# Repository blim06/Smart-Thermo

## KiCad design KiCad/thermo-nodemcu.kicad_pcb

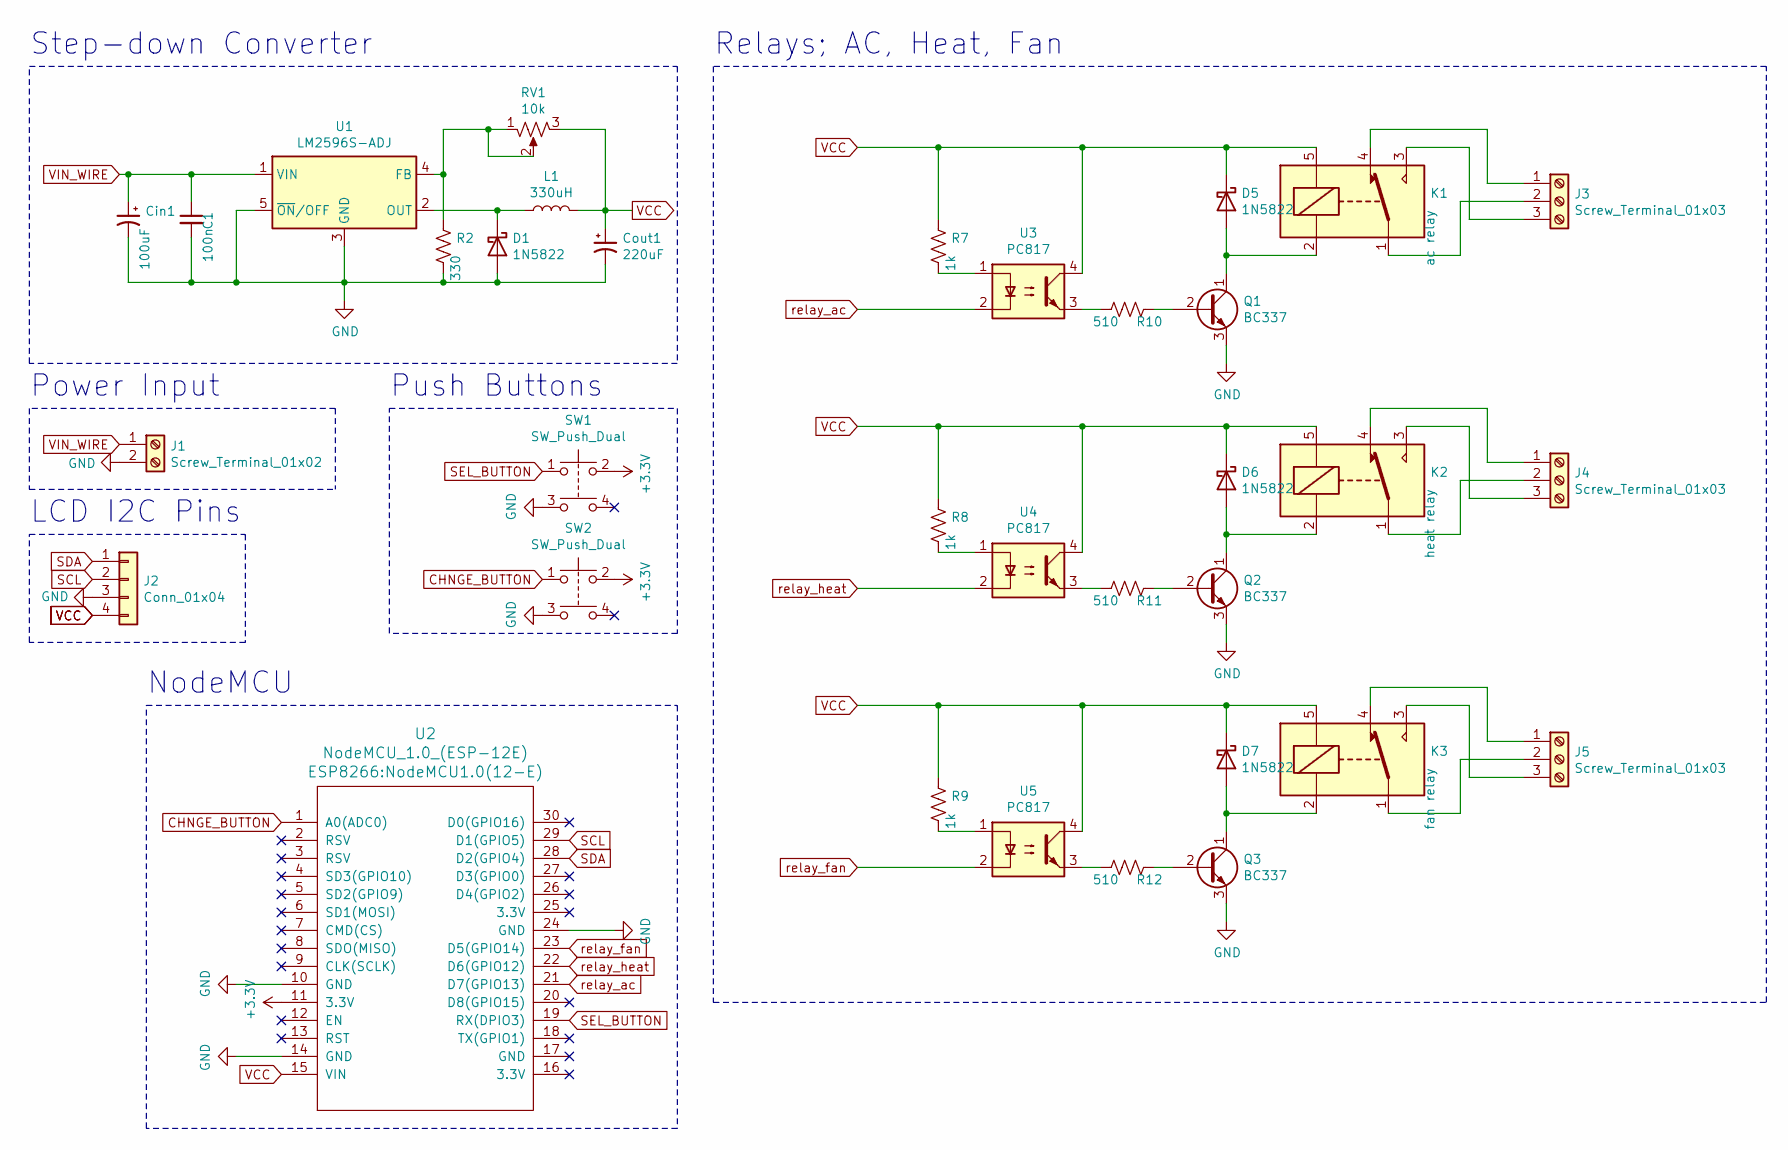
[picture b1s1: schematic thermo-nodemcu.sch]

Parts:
C1: 100n; C_0805_2012Metric
Cin1: 100uF; CP_Radial_D8.0mm_P3.50mm
Cout1: 220uF; CP_Radial_D6.3mm_P2.50mm
D1, D5, D6, D7: 1N5822; D_DO-201AD_P15.24mm_Horizontal
J1: Screw_Terminal_01x02; Altech_AK300_1x02_P5.00mm_45-Degree
J2: Conn_01x04; PinSocket_1x04_P1.27mm_Vertical
J3, J4, J5: Screw_Terminal_01x03; Altech_AK300_1x03_P5.00mm_45-Degree
K1: ac relay; Relay_SPDT_SANYOU_SRD_Series_Form_C
K2: heat relay; Relay_SPDT_SANYOU_SRD_Series_Form_C
K3: fan relay; Relay_SPDT_SANYOU_SRD_Series_Form_C
L1: 330uH; L_0805_2012Metric
Q1, Q2, Q3: BC337; TO-92_Inline
R2: 330; R_0805_2012Metric
R7, R8, R9: 1k; R_0805_2012Metric
R10, R11, R12: 510; R_0805_2012Metric
RV1: 10k; Potentiometer_Bourns_3296W_Vertical
SW1, SW2: SW_Push_Dual; PinSocket_2x02_P1.27mm_Vertical
U1: LM2596S-ADJ; TO-263-5_TabPin3
U2: NodeMCU_1.0_(ESP-12E); NodeMCU1.0(12-E)
U3, U4, U5: PC817; DIP-4_W7.62mm

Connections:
+3V3: SW1.2, SW2.2, U2.11 (3.3V)
CHNGE_BUTTON: SW2.1, U2.1 (A0(ADC0))
GND: C1.2, Cin1.2, Cout1.2, D1.2 (A), J1.2, J2.3, Q1.3 (E), Q2.3 (E), Q3.3 (E), R2.2, SW1.3, SW2.3, U1.3 (GND), U1.5 (~ON~/OFF), U2.10 (GND), U2.14 (GND), U2.24 (GND)
unnamed: D1.1 (K), L1.2, U1.2 (OUT)
unnamed: D5.2 (A), K1.2, Q1.1 (C)
unnamed: D6.2 (A), K2.2, Q2.1 (C)
unnamed: D7.2 (A), K3.2, Q3.1 (C)
unnamed: J3.1, K1.4
unnamed: J3.2, K1.1
unnamed: J3.3, K1.3
unnamed: J4.1, K2.4
unnamed: J4.2, K2.1
unnamed: J4.3, K2.3
unnamed: J5.1, K3.4
unnamed: J5.2, K3.1
unnamed: J5.3, K3.3
unnamed: Q1.2 (B), R10.1
unnamed: Q2.2 (B), R11.1
unnamed: Q3.2 (B), R12.1
unnamed: R2.1, RV1.1, RV1.2, U1.4 (FB)
unnamed: R7.2, U3.1
unnamed: R8.2, U4.1
unnamed: R9.2, U5.1
unnamed: R10.2, U3.3
unnamed: R11.2, U4.3
unnamed: R12.2, U5.3
SCL: J2.2, U2.29 (D1(GPIO5))
SDA: J2.1, U2.28 (D2(GPIO4))
SEL_BUTTON: SW1.1, U2.19 (RX(DPIO3))
VCC: Cout1.1, D5.1 (K), D6.1 (K), D7.1 (K), J2.4, K1.5, K2.5, K3.5, L1.1, R7.1, R8.1, R9.1, RV1.3, U2.15 (VIN), U3.4, U4.4, U5.4
VIN_WIRE: C1.1, Cin1.1, J1.1, U1.1 (VIN)
relay_ac: U2.21 (D7(GPIO13)), U3.2
relay_fan: U2.23 (D5(GPIO14)), U5.2
relay_heat: U2.22 (D6(GPIO12)), U4.2

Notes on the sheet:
Power Input
Push Buttons
Relays; AC, Heat, Fan
Step-down Converter
LCD I2C Pins
NodeMCU

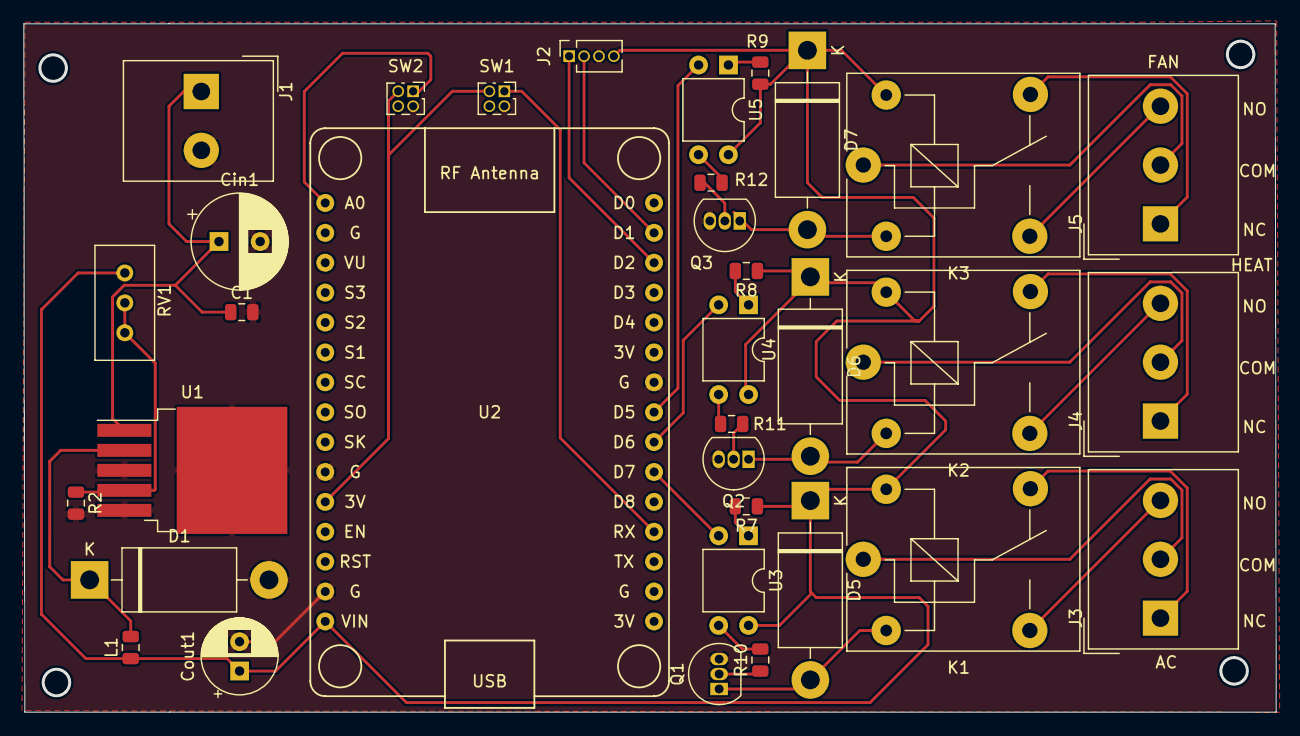
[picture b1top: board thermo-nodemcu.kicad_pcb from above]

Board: 2 copper layers, 106.4 x 58.5 mm, 34 parts (0 on the bottom side), 34 nets.

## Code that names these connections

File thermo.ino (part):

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#define DEBUG 1

//pins for relays
#define relay_ac 14     // relay 1 pins for relay that controls heat & ac (D5)
#define relay_heat 12   // relay 2 D6
#define relay_fan 13    // relay 3 D7 fan
#define buttonUpPin 3
//const int buttonDownPin
#define buttonSelectPin A0
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  // put your setup code here, to run once:

  Serial.begin(115200);
  pinMode(relay_ac, OUTPUT);
  pinMode(relay_heat, OUTPUT);  
  pinMode(relay_fan, OUTPUT);
  pinMode(buttonUpPin, INPUT);
  pinMode(buttonSelectPin, INPUT);

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
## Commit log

2020-09-22 Initial
